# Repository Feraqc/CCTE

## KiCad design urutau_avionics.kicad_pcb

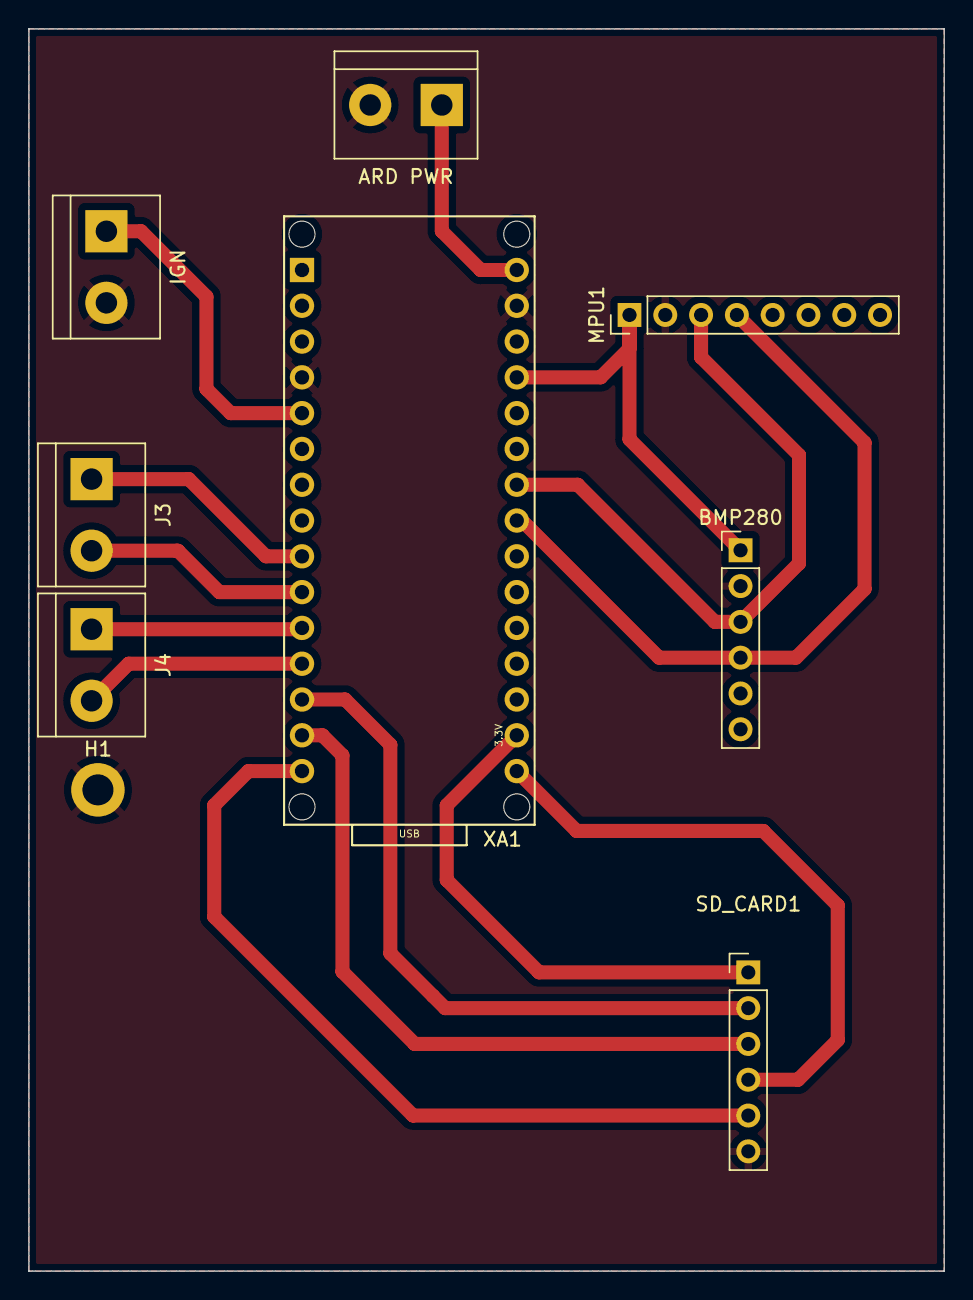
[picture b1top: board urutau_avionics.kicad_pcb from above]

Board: 2 copper layers, 65.0 x 88.1 mm, 9 parts (0 on the bottom side), 15 nets.

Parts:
ARD PWR: ARD PWR; TerminalBlock_bornier-2_P5.08mm
BMP280: Conn_01x06_Male; PinHeader_1x06_P2.54mm_Vertical
H1: GND; MountingHole_2.2mm_M2_DIN965_Pad
IGN: IGN; TerminalBlock_bornier-2_P5.08mm
J3: LED STATE 1; TerminalBlock_bornier-2_P5.08mm
J4: LED STATE 2; TerminalBlock_bornier-2_P5.08mm
MPU1: Conn_01x08_Male; PinHeader_1x08_P2.54mm_Vertical
SD_CARD1: Conn_01x06_Male; PinHeader_1x06_P2.54mm_Vertical
XA1: Arduino_Nano_Socket

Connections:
+3.3V: SD_CARD1.1, XA1.3V3 (3.3V)
+5V: BMP280.1, MPU1.1, XA1.5V
+9V: ARD PWR.1, XA1.VIN
CS: SD_CARD1.2, XA1.D10 (D10_CS)
GND: ARD PWR.2, BMP280.2, H1.1, IGN.2, MPU1.2, SD_CARD1.6, XA1.GND1 (GND), XA1.GND2 (GND)
I2C_CLK: BMP280.3, MPU1.3, XA1.A5 (A5_SCL)
I2C_DA: BMP280.4, MPU1.4, XA1.A4 (A4_SDA)
IGN: IGN.1, XA1.D2 (D2_INT0)
MISO: SD_CARD1.5, XA1.D12 (D12_MISO)
MOSI: SD_CARD1.3, XA1.D11 (D11_MOSI)
S0: J3.1, XA1.D6
S1: J3.2, XA1.D7
S2: J4.1, XA1.D8
S3: J4.2, XA1.D9
SCK: SD_CARD1.4, XA1.D13 (D13_SCK)

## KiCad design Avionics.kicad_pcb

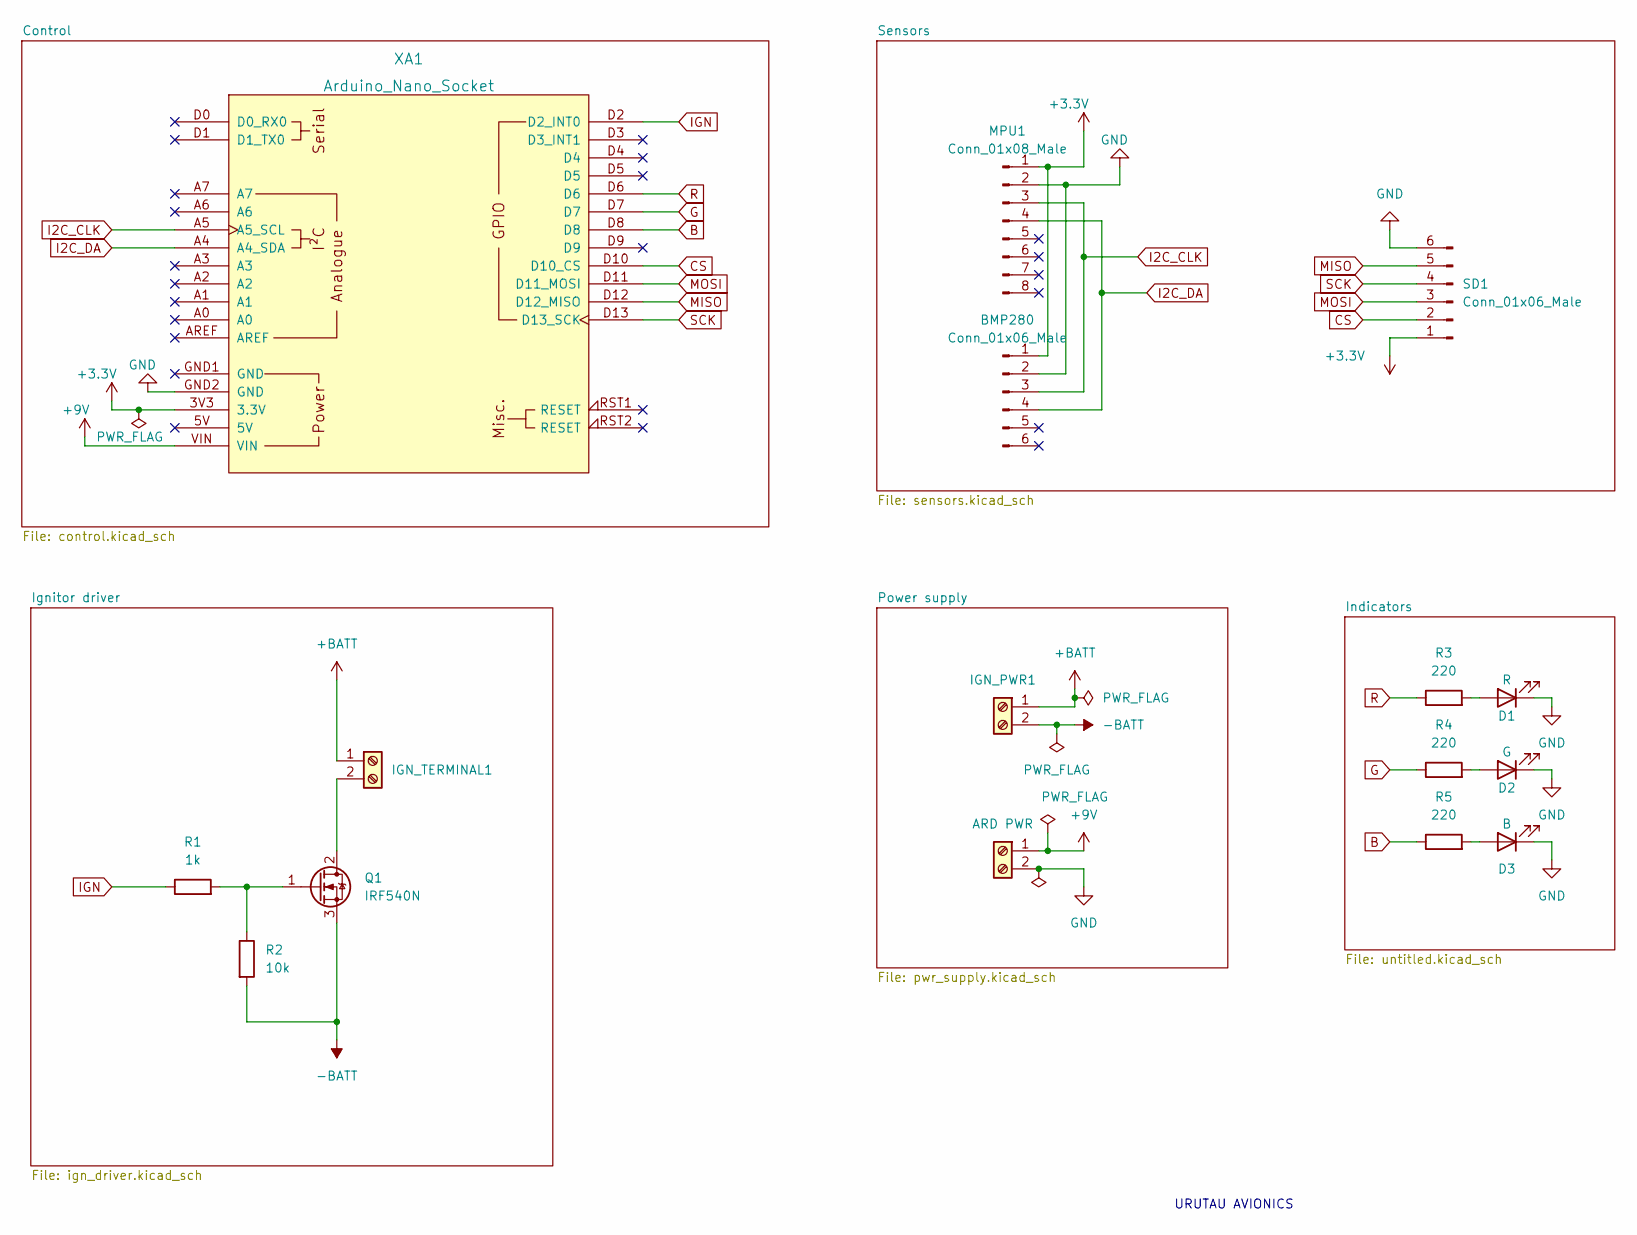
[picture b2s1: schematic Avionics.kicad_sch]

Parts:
BMP280: Conn_01x06_Male; PinHeader_1x06_P1.27mm_Vertical
D1: R; LED_D3.0mm_Clear
D2: G; LED_D3.0mm_Clear
D3: B
IGN_PWR1: IGN_PWR; TerminalBlock_bornier-2_P5.08mm
IGN_TERMINAL1: Ignitor wires; TerminalBlock_bornier-2_P5.08mm
J1: ARD PWR; TerminalBlock_bornier-2_P5.08mm
MPU1: Conn_01x08_Male; PinHeader_1x08_P1.27mm_Vertical
Q1: IRF540N; TO-220-3_Vertical
R1: 1k; R_Axial_DIN0204_L3.6mm_D1.6mm_P5.08mm_Horizontal
R2: 10k; R_Axial_DIN0204_L3.6mm_D1.6mm_P5.08mm_Horizontal
R3, R4, R5: 220; R_Axial_DIN0204_L3.6mm_D1.6mm_P5.08mm_Horizontal
SD1: Conn_01x06_Male; PinHeader_1x06_P1.27mm_Vertical
XA1: Arduino_Nano_Socket

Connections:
+3.3V: BMP280.1, MPU1.1, SD1.1, XA1.3V3 (3.3V)
+9V: J1.1, XA1.VIN
+BATT: IGN_PWR1.1, IGN_TERMINAL1.1
-BATT: IGN_PWR1.2, Q1.3 (S), R2.2
B: R5.1, XA1.D8
CS: SD1.2, XA1.D10 (D10_CS)
G: R4.1, XA1.D7
GND: BMP280.2, D1.1 (K), D2.1 (K), D3.1 (K), J1.2, MPU1.2, SD1.6, XA1.GND2 (GND)
I2C_CLK: BMP280.3, MPU1.3, XA1.A5 (A5_SCL)
I2C_DA: BMP280.4, MPU1.4, XA1.A4 (A4_SDA)
IGN: R1.1, XA1.D2 (D2_INT0)
MISO: SD1.5, XA1.D12 (D12_MISO)
MOSI: SD1.3, XA1.D11 (D11_MOSI)
unnamed: D1.2 (A), R3.2
unnamed: D2.2 (A), R4.2
unnamed: D3.2 (A), R5.2
unnamed: IGN_TERMINAL1.2, Q1.2 (D)
unnamed: Q1.1 (G), R1.2, R2.1
R: R3.1, XA1.D6
SCK: SD1.4, XA1.D13 (D13_SCK)

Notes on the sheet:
URUTAU AVIONICS

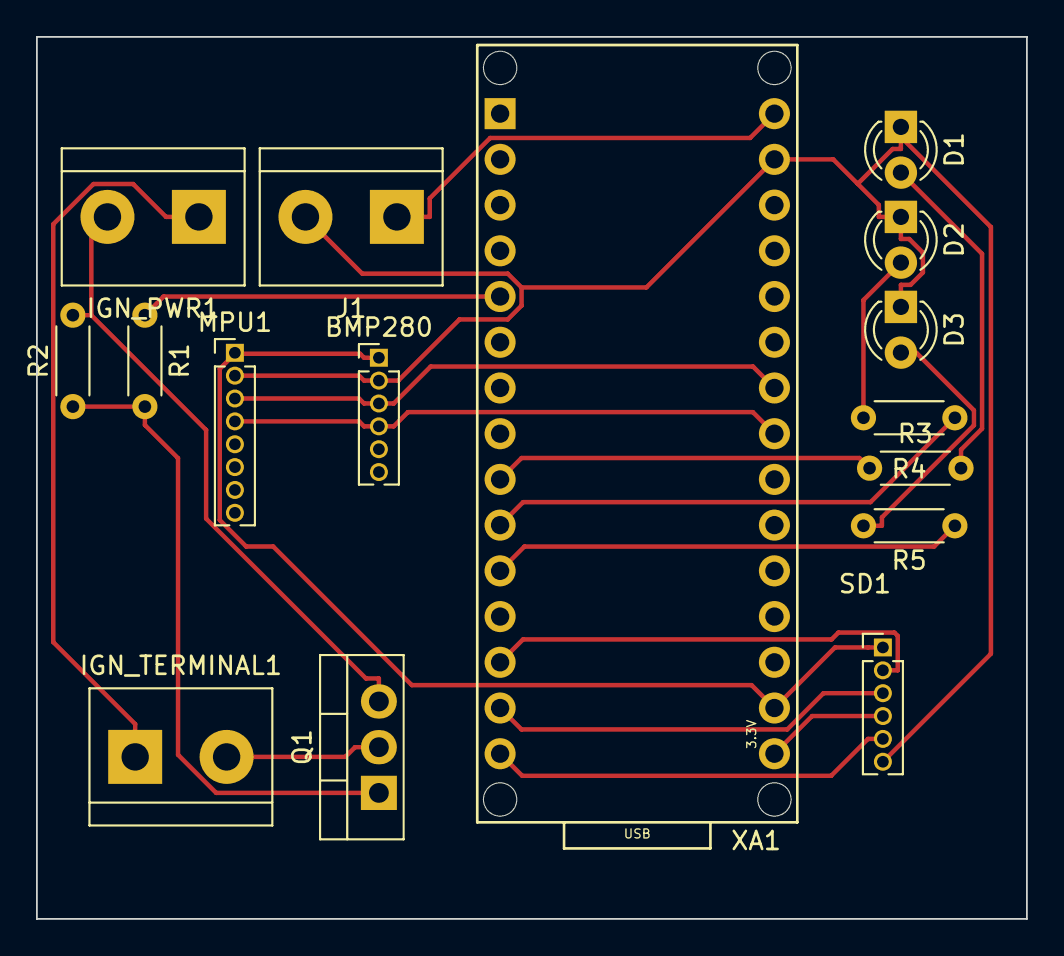
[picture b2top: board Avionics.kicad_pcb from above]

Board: 2 copper layers, 55.0 x 49.0 mm, 16 parts (0 on the bottom side), 20 nets.
